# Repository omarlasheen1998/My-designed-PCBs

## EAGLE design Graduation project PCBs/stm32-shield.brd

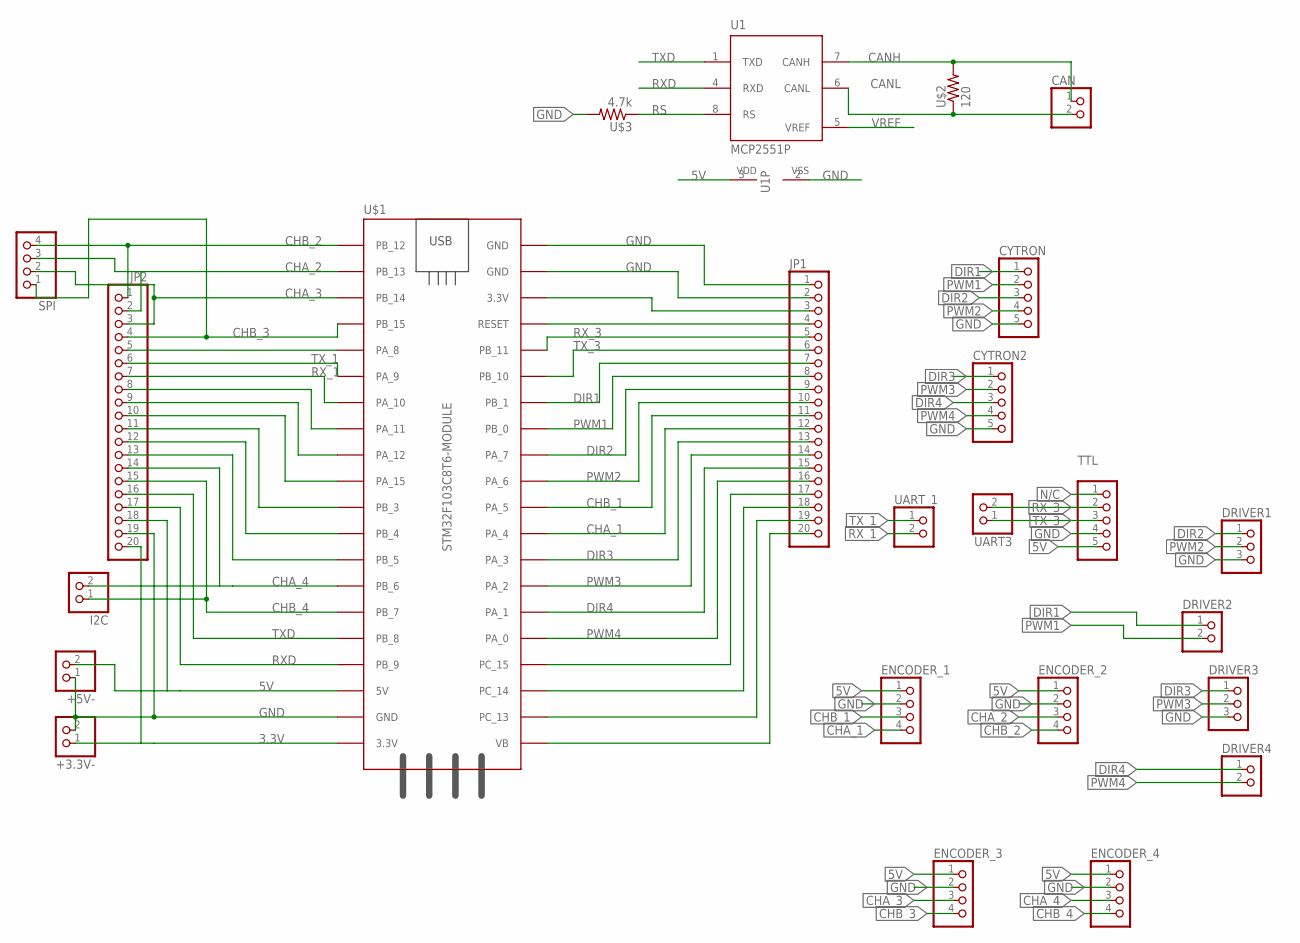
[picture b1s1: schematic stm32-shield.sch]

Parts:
+3.3V-, +5V-: PINHD-2_DATA; 1X02_DATA
CAN: PINHD-2_DATA; 1X02_DATA
CYTRON, CYTRON2: PINHD-5_DATA; 1X05_DATA
DRIVER1, DRIVER3: PINHD-3_DATA; 1X03_DATA
DRIVER2, DRIVER4: PINHD-2_DATA; 1X02_DATA
ENCODER_1, ENCODER_2, ENCODER_3, ENCODER_4: PINHD-4_DATA; 1X04_DATA
I2C: PINHD-2_DATA; 1X02_DATA
JP1, JP2: PINHD-1X20; 1X20
SPI: PINHD-4_DATA; 1X04_DATA
TTL: PINHD-5_DATA; 1X05_DATA
U1: MCP2551P; DIL8
U$1: STM32F103C8T6-MODULE
U$2: 120; 0204/7
U$3: 4.7k; 0204/7
UART3: PINHD-2_DATA; 1X02_DATA
UART_1: PINHD-2_DATA; 1X02_DATA

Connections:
3.3V: +3.3V-.1, JP2.20, U$1.3.3V_1 (3.3V)
5V: +5V-.2, ENCODER_1.1, ENCODER_2.1, ENCODER_3.1, ENCODER_4.1, JP2.18, TTL.5, U1.3 (VDD), U$1.5V
ADADA: JP2.5, U$1.PA_8
ARQRQ: JP2.13, U$1.PB_5
CANH: CAN.1, U1.7 (CANH), U$2.2
CANL: CAN.2, U1.6 (CANL), U$2.1
CHA_1: ENCODER_1.4, JP1.12, U$1.PA_4
CHA_2: ENCODER_2.3, JP2.2, SPI.3, U$1.PB_13
CHA_3: ENCODER_3.3, JP2.3, SPI.2, U$1.PB_14
CHA_4: ENCODER_4.3, I2C.2, JP2.14, U$1.PB_6
CHB_1: ENCODER_1.3, JP1.11, U$1.PA_5
CHB_2: ENCODER_2.4, JP2.1, SPI.4, U$1.PB_12
CHB_3: ENCODER_3.4, JP2.4, SPI.1, U$1.PB_15
CHB_4: ENCODER_4.4, I2C.1, JP2.15, U$1.PB_7
DIR1: CYTRON.1, DRIVER2.1, JP1.7, U$1.PB_1
DIR2: CYTRON.3, DRIVER1.1, JP1.9, U$1.PA_7
DIR3: CYTRON2.1, DRIVER3.1, JP1.13, U$1.PA_3
DIR4: CYTRON2.3, DRIVER4.1, JP1.15, U$1.PA_1
GND: +3.3V-.2, +5V-.1, CYTRON.5, CYTRON2.5, DRIVER1.3, DRIVER3.3, ENCODER_1.2, ENCODER_2.2, ENCODER_3.2, ENCODER_4.2, JP1.1, JP1.2, JP2.19, TTL.4, U1.2 (VSS), U$1.GND_1 (GND), U$1.GND_2 (GND), U$1.GND_3 (GND), U$3.2
unnamed: JP1.3, U$1.3.3V_2 (3.3V)
unnamed: JP1.4, U$1.RESET
unnamed: JP1.17, U$1.PC_15
unnamed: JP1.18, U$1.PC_14
unnamed: JP1.19, U$1.PC_13
unnamed: JP1.20, U$1.VB
unnamed: JP2.8, U$1.PA_11
unnamed: JP2.9, U$1.PA_12
unnamed: JP2.10, U$1.PA_15
unnamed: JP2.11, U$1.PB_3
unnamed: JP2.12, U$1.PB_4
N/C: TTL.1
PWM1: CYTRON.2, DRIVER2.2, JP1.8, U$1.PB_0
PWM2: CYTRON.4, DRIVER1.2, JP1.10, U$1.PA_6
PWM3: CYTRON2.2, DRIVER3.2, JP1.14, U$1.PA_2
PWM4: CYTRON2.4, DRIVER4.2, JP1.16, U$1.PA_0
RS: U1.8 (RS), U$3.1
RXD: JP2.17, U1.4 (RXD), U$1.PB_9
RX_1: JP2.7, U$1.PA_10, UART_1.2
RX_3: JP1.5, TTL.2, U$1.PB_11, UART3.2
TXD: JP2.16, U1.1 (TXD), U$1.PB_8
TX_1: JP2.6, U$1.PA_9, UART_1.1
TX_3: JP1.6, TTL.3, U$1.PB_10, UART3.1
VREF: U1.5 (VREF)

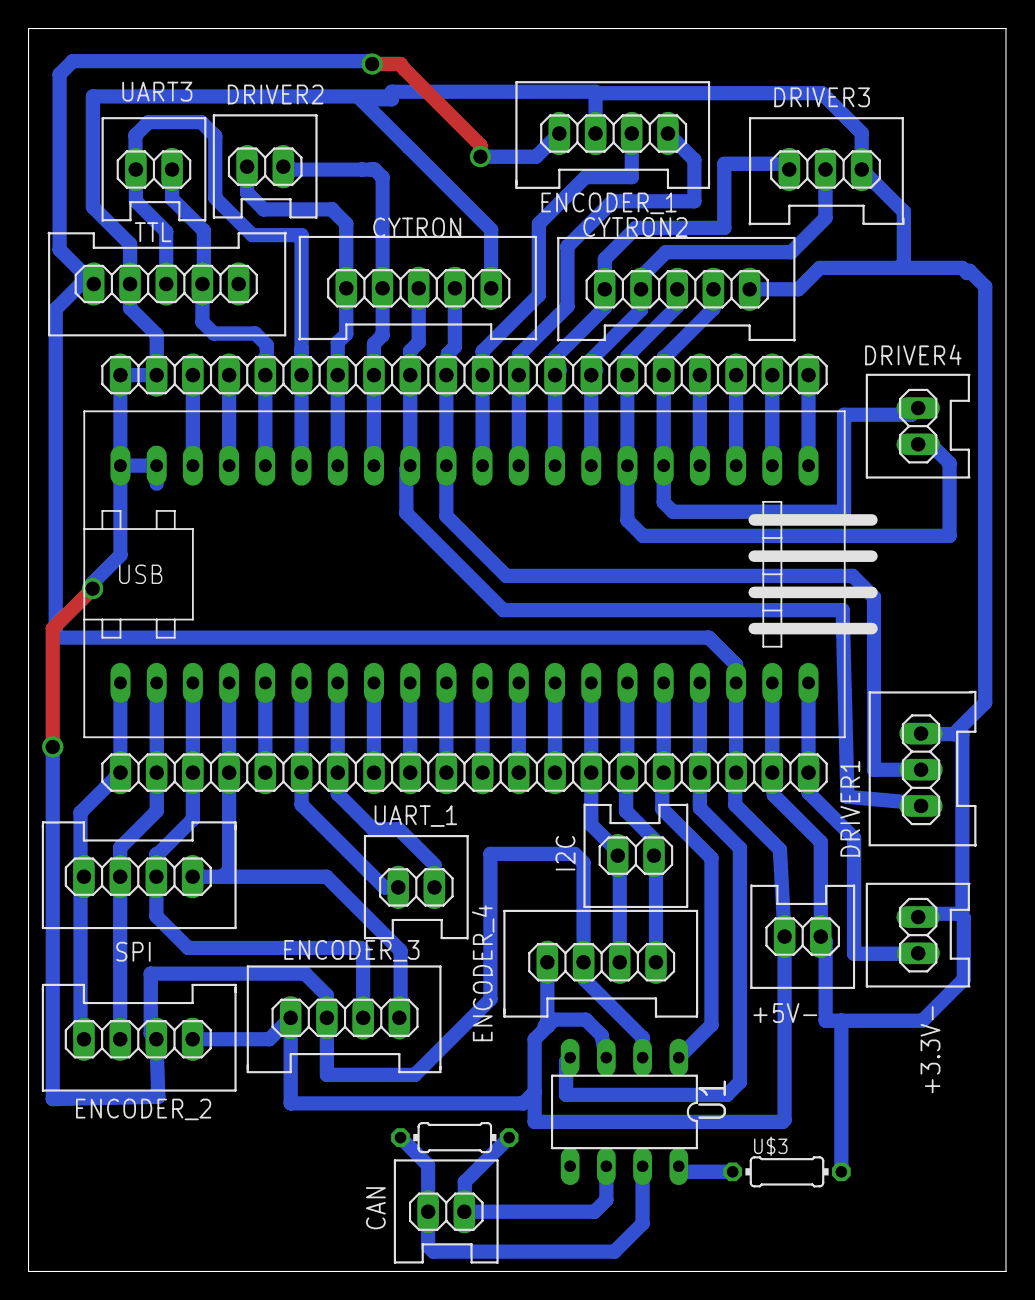
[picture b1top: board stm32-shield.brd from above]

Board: 2 copper layers, 68.6 x 87.2 mm, 24 parts (0 on the bottom side), 41 nets.

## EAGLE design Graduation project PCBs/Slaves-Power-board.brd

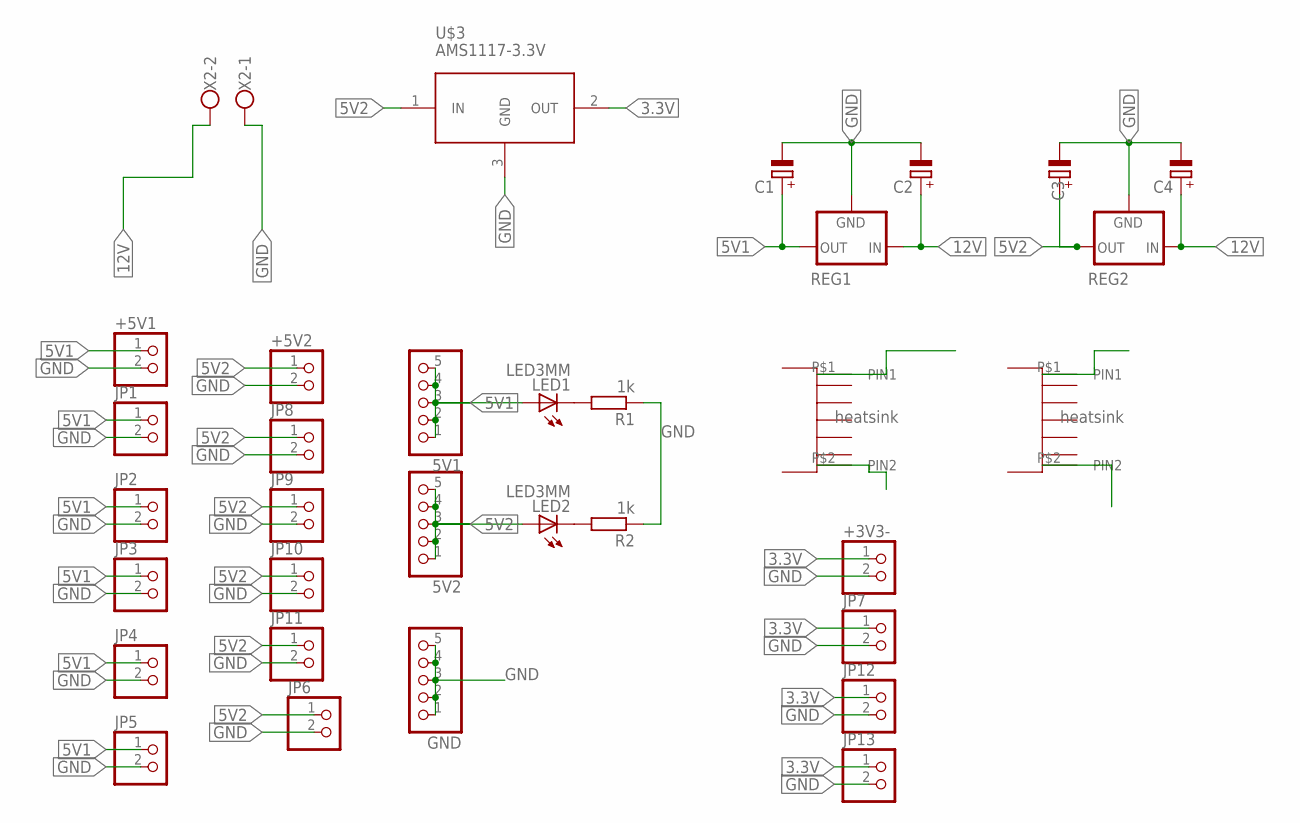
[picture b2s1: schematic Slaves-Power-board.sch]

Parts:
5V1, 5V2: PINHD-1X5; 1X05
+3V3-, +5V1, +5V2: PINHD-2_DATA; 1X02_DATA
C1, C2, C3, C4: CAP_POL; E3,5-8
GND: PINHD-1X5; 1X05
JP1, JP2, JP3, JP4, JP5, JP6, JP7, JP8, JP9, JP10, JP11, JP12, JP13: PINHD-2_DATA; 1X02_DATA
LED1, LED2: LED3MM
R1, R2: 1k; 0204/7
REG1, REG2: 78XXS
U$1, U$2: HEAT-SINK; HEAT_SINK
U$3: AMS1117-3.3V; REG-AMS1117-3P#V
X2: ROSTA.POWER; W239-302

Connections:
3.3V: +3V3-.1, JP7.1, JP12.1, JP13.1, U$3.2 (OUT)
5V1: 5V1.1, 5V1.2, 5V1.3, 5V1.4, 5V1.5, +5V1.1, C1.+, JP1.1, JP2.1, JP3.1, JP4.1, JP5.1, LED1.A, REG1.OUT
5V2: 5V2.1, 5V2.2, 5V2.3, 5V2.4, 5V2.5, +5V2.1, C3.+, JP6.1, JP8.1, JP9.1, JP10.1, JP11.1, LED2.A, REG2.OUT, U$3.1 (IN)
12V: C2.+, C4.+, REG1.IN, REG2.IN, X2.2
GND: +3V3-.2, +5V1.2, +5V2.2, C1.-, C2.-, C3.-, C4.-, GND.1, GND.2, GND.3, GND.4, GND.5, JP1.2, JP2.2, JP3.2, JP4.2, JP5.2, JP6.2, JP7.2, JP8.2, JP9.2, JP10.2, JP11.2, JP12.2, JP13.2, R1.1, R2.1, REG1.GND, REG2.GND, U$3.3 (GND), X2.1
unnamed: LED1.K (C), R1.2
unnamed: LED2.K (C), R2.2

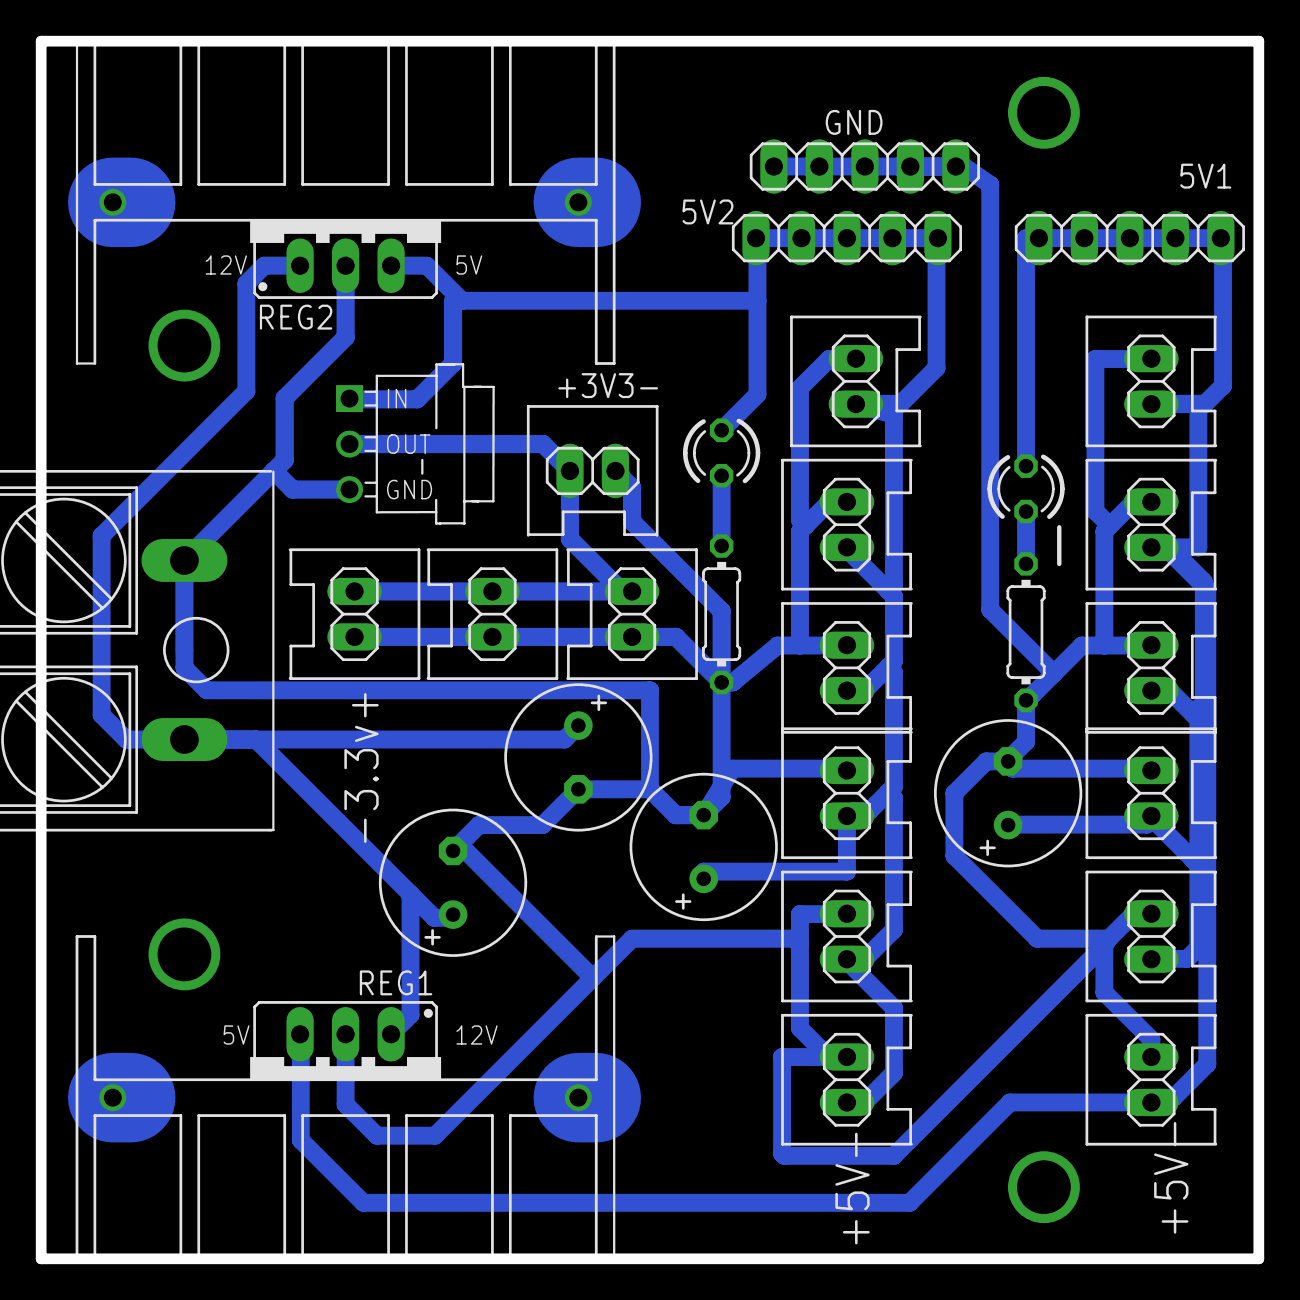
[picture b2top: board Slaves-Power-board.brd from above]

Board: 2 copper layers, 68.0 x 68.0 mm, 33 parts (0 on the bottom side), 7 nets.

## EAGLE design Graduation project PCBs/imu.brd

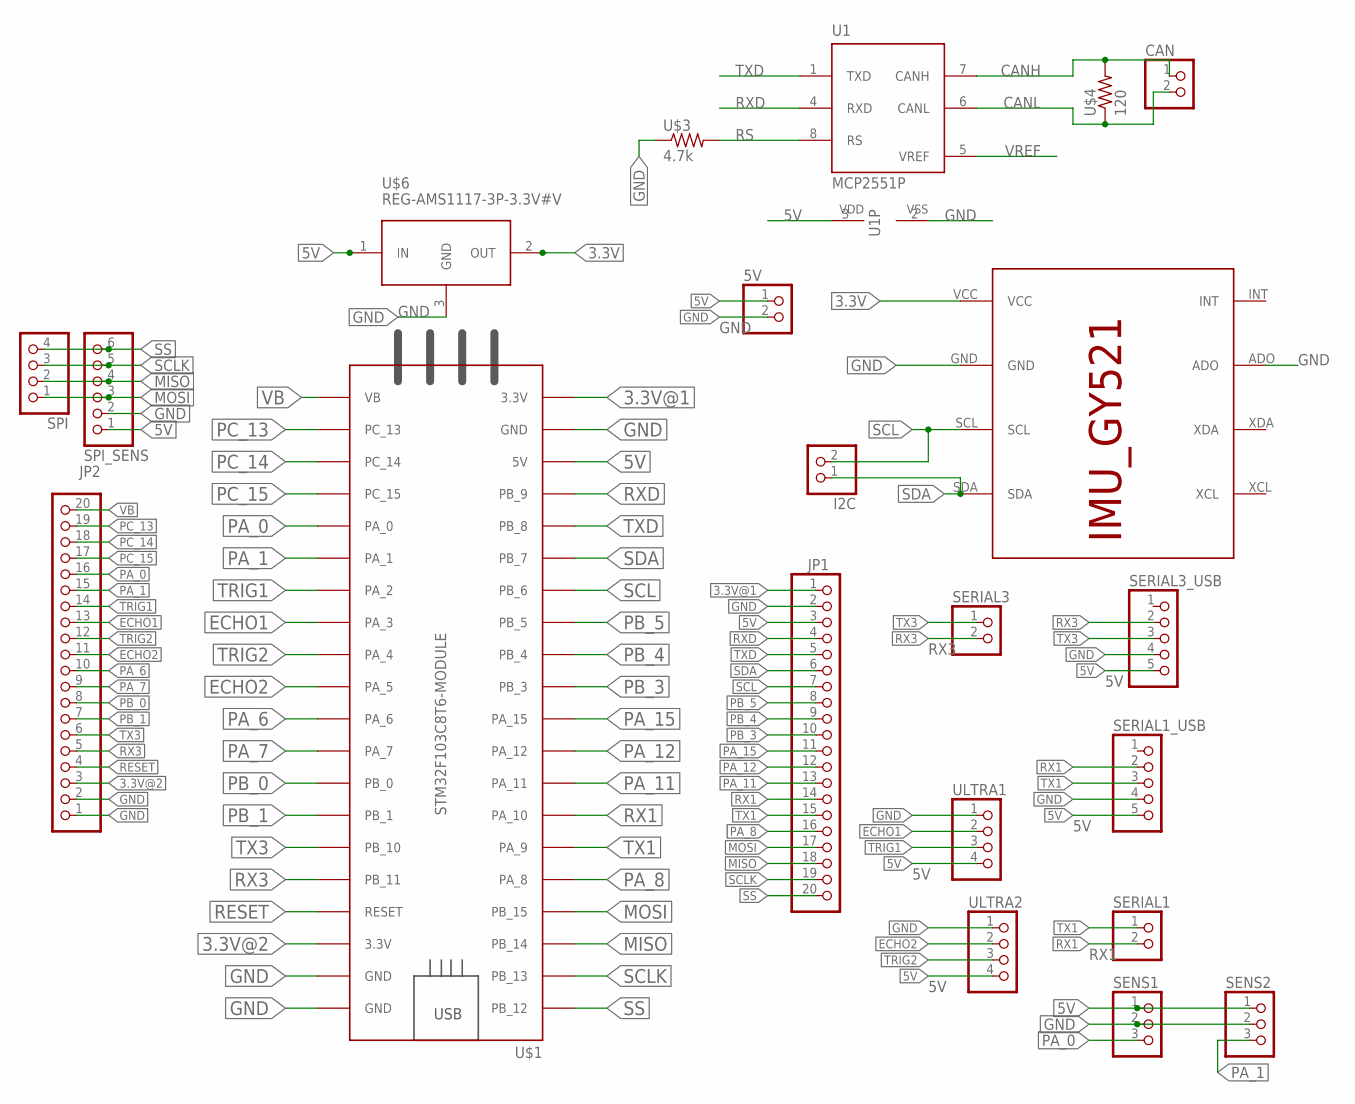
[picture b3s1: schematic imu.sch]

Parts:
5V: PINHD-2_DATA; 1X02_DATA
CAN: PINHD-2_DATA; 1X02_DATA
I2C: PINHD-2_DATA; 1X02_DATA
JP1, JP2: PINHD-1X20; 1X20
SENS1, SENS2: PINHD-3_DATA; 1X03_DATA
SERIAL1, SERIAL3: PINHD-2_DATA; 1X02_DATA
SERIAL1_USB, SERIAL3_USB: PINHD-5_DATA; 1X05_DATA
SPI: PINHD-4_DATA; 1X04_DATA
SPI_SENS: PINHD-6_DATA; 1X06_DATA
U1: MCP2551P; DIL8
U$1: STM32F103C8T6-MODULE
U$2: IMU_MPU6050; IMU_GY521
U$3: 4.7k; 0204/7
U$4: 120; 0204/7
U$6: REG-AMS1117-3P-3.3V#V; REG-AMS1117-3P#V
ULTRA1, ULTRA2: PINHD-4_DATA; 1X04_DATA

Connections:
3.3V: U$2.VCC, U$6.2 (OUT)
3.3V@1: JP1.1, U$1.3.3V_1 (3.3V)
3.3V@2: JP2.3, U$1.3.3V_2 (3.3V)
5V: 5V.1, JP1.3, SENS1.1, SENS2.1, SERIAL1_USB.5, SERIAL3_USB.5, SPI_SENS.1, U1.3 (VDD), U$1.5V, U$6.1 (IN), ULTRA1.4, ULTRA2.4
CANH: CAN.1, U1.7 (CANH), U$4.2
CANL: CAN.2, U1.6 (CANL), U$4.1
ECHO1: JP2.13, U$1.PA_3, ULTRA1.2
ECHO2: JP2.11, U$1.PA_5, ULTRA2.2
GND: 5V.2, JP1.2, JP2.1, JP2.2, SENS1.2, SENS2.2, SERIAL1_USB.4, SERIAL3_USB.4, SPI_SENS.2, U1.2 (VSS), U$1.GND_1 (GND), U$1.GND_2 (GND), U$1.GND_3 (GND), U$2.ADO, U$2.GND, U$3.1, U$6.3 (GND), ULTRA1.1, ULTRA2.1
MISO: JP1.18, SPI.2, SPI_SENS.4, U$1.PB_14
MOSI: JP1.17, SPI.1, SPI_SENS.3, U$1.PB_15
PA_0: JP2.16, SENS1.3, U$1.PA_0
PA_1: JP2.15, SENS2.3, U$1.PA_1
PA_6: JP2.10, U$1.PA_6
PA_7: JP2.9, U$1.PA_7
PA_8: JP1.16, U$1.PA_8
PA_11: JP1.13, U$1.PA_11
PA_12: JP1.12, U$1.PA_12
PA_15: JP1.11, U$1.PA_15
PB_0: JP2.8, U$1.PB_0
PB_1: JP2.7, U$1.PB_1
PB_3: JP1.10, U$1.PB_3
PB_4: JP1.9, U$1.PB_4
PB_5: JP1.8, U$1.PB_5
PC_13: JP2.19, U$1.PC_13
PC_14: JP2.18, U$1.PC_14
PC_15: JP2.17, U$1.PC_15
RESET: JP2.4, U$1.RESET
RS: U1.8 (RS), U$3.2
RX1: JP1.14, SERIAL1.2, SERIAL1_USB.2, U$1.PA_10
RX3: JP2.5, SERIAL3.2, SERIAL3_USB.2, U$1.PB_11
RXD: JP1.4, U1.4 (RXD), U$1.PB_9
SCL: I2C.2, JP1.7, U$1.PB_6, U$2.SCL
SCLK: JP1.19, SPI.3, SPI_SENS.5, U$1.PB_13
SDA: I2C.1, JP1.6, U$1.PB_7, U$2.SDA
SS: JP1.20, SPI.4, SPI_SENS.6, U$1.PB_12
TRIG1: JP2.14, U$1.PA_2, ULTRA1.3
TRIG2: JP2.12, U$1.PA_4, ULTRA2.3
TX1: JP1.15, SERIAL1.1, SERIAL1_USB.3, U$1.PA_9
TX3: JP2.6, SERIAL3.1, SERIAL3_USB.3, U$1.PB_10
TXD: JP1.5, U1.1 (TXD), U$1.PB_8
VB: JP2.20, U$1.VB
VREF: U1.5 (VREF)

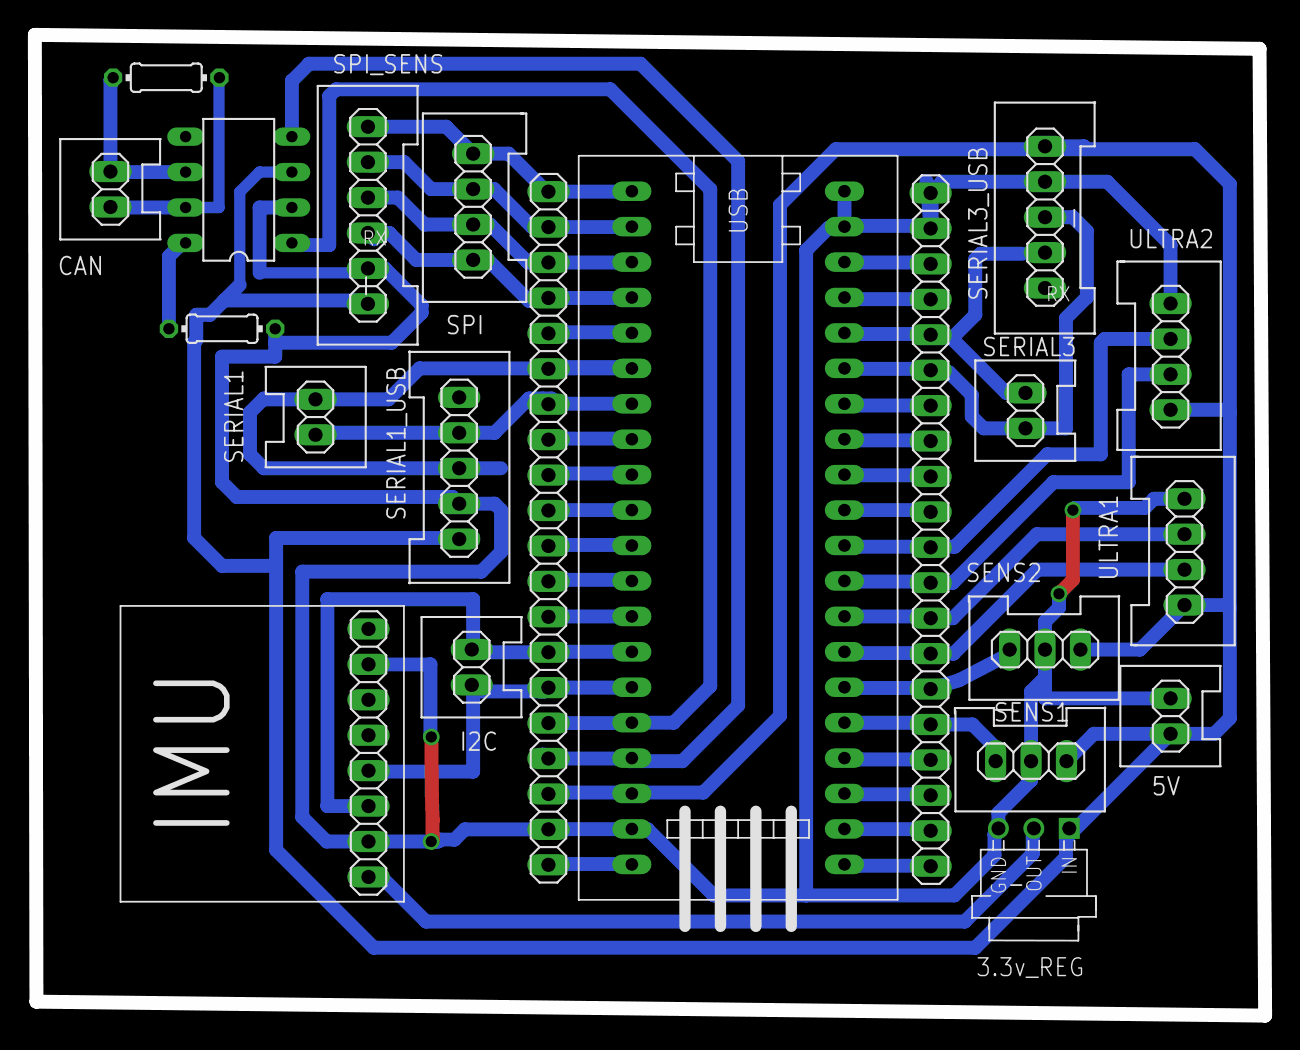
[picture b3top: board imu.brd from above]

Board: 2 copper layers, 88.2 x 70.3 mm, 21 parts (0 on the bottom side), 42 nets.

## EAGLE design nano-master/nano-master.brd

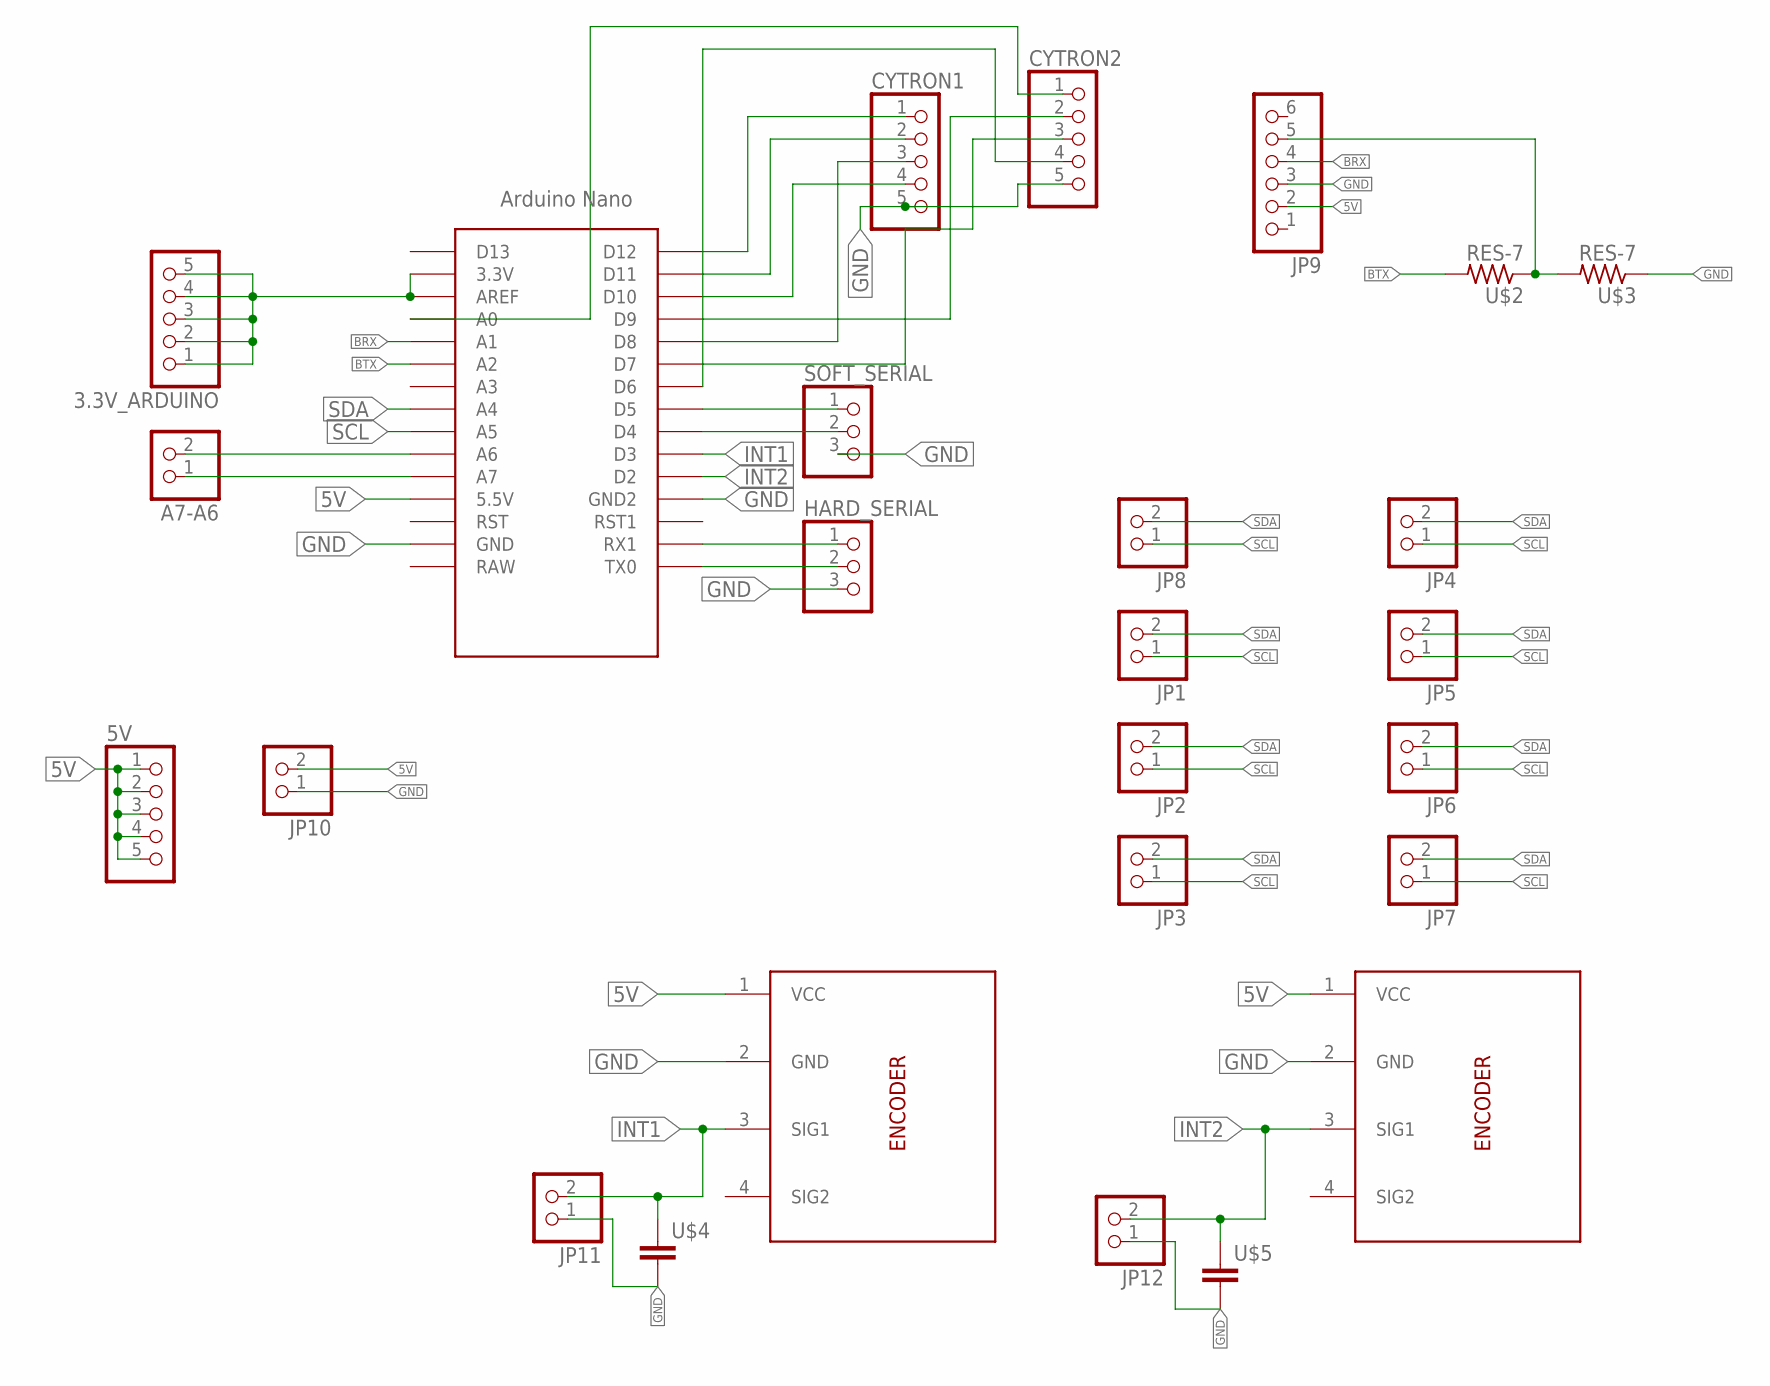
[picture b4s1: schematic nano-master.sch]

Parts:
3.3V_ARDUINO, 5V: PINHD-1X5; 1X05
A7-A6: PINHD-1X2; 1X02
CYTRON1, CYTRON2: PINHD-1X5; 1X05
ENCODER1, ENCODER2: ENCODER; 1X04
HARD_SERIAL: PINHD-1X3; 1X03
JP1, JP2, JP3, JP4, JP5, JP6, JP7, JP8, JP10, JP11, JP12: PINHD-2_DATA; 1X02
JP9: PINHD-1X6; 1X06
SOFT_SERIAL: PINHD-1X3; 1X03
U$1: NANO
U$2, U$3: RES-7; 0204/7
U$4, U$5: CAPACITOR; C025-025X050

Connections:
5V: 5V.1, 5V.2, 5V.3, 5V.4, 5V.5, ENCODER1.1 (VCC), ENCODER2.1 (VCC), JP9.2, JP10.2, U$1.5V (5.5V)
BRX: JP9.4, U$1.A1
BTX: U$1.A2, U$2.2
GND: CYTRON1.5, CYTRON2.5, ENCODER1.2 (GND), ENCODER2.2 (GND), HARD_SERIAL.3, JP9.3, JP10.1, JP11.1, JP12.1, SOFT_SERIAL.3, U$1.GND, U$1.GND1 (GND2), U$3.1, U$4.2, U$5.2
INT1: ENCODER2.3 (SIG1), JP11.2, U$1.D3, U$4.1
INT2: ENCODER1.3 (SIG1), JP12.2, U$1.D2, U$5.1
unnamed: SOFT_SERIAL.1, U$1.D5
unnamed: SOFT_SERIAL.2, U$1.D4
unnamed: HARD_SERIAL.1, U$1.RX1
unnamed: HARD_SERIAL.2, U$1.TX0
unnamed: CYTRON1.1, U$1.D12
unnamed: CYTRON1.2, U$1.D11
unnamed: CYTRON1.4, U$1.D10
unnamed: CYTRON2.2, U$1.D9
unnamed: CYTRON1.3, U$1.D8
unnamed: CYTRON2.3, U$1.D7
unnamed: CYTRON2.4, U$1.D6
unnamed: CYTRON2.1, U$1.A0
unnamed: JP9.5, U$2.1, U$3.2
unnamed: A7-A6.1, U$1.A7
unnamed: A7-A6.2, U$1.A6
unnamed: 3.3V_ARDUINO.1, 3.3V_ARDUINO.2, 3.3V_ARDUINO.3, 3.3V_ARDUINO.4, 3.3V_ARDUINO.5, U$1.3.3V, U$1.AREF
SCL: JP1.1, JP2.1, JP3.1, JP4.1, JP5.1, JP6.1, JP7.1, JP8.1, U$1.A5
SDA: JP1.2, JP2.2, JP3.2, JP4.2, JP5.2, JP6.2, JP7.2, JP8.2, U$1.A4

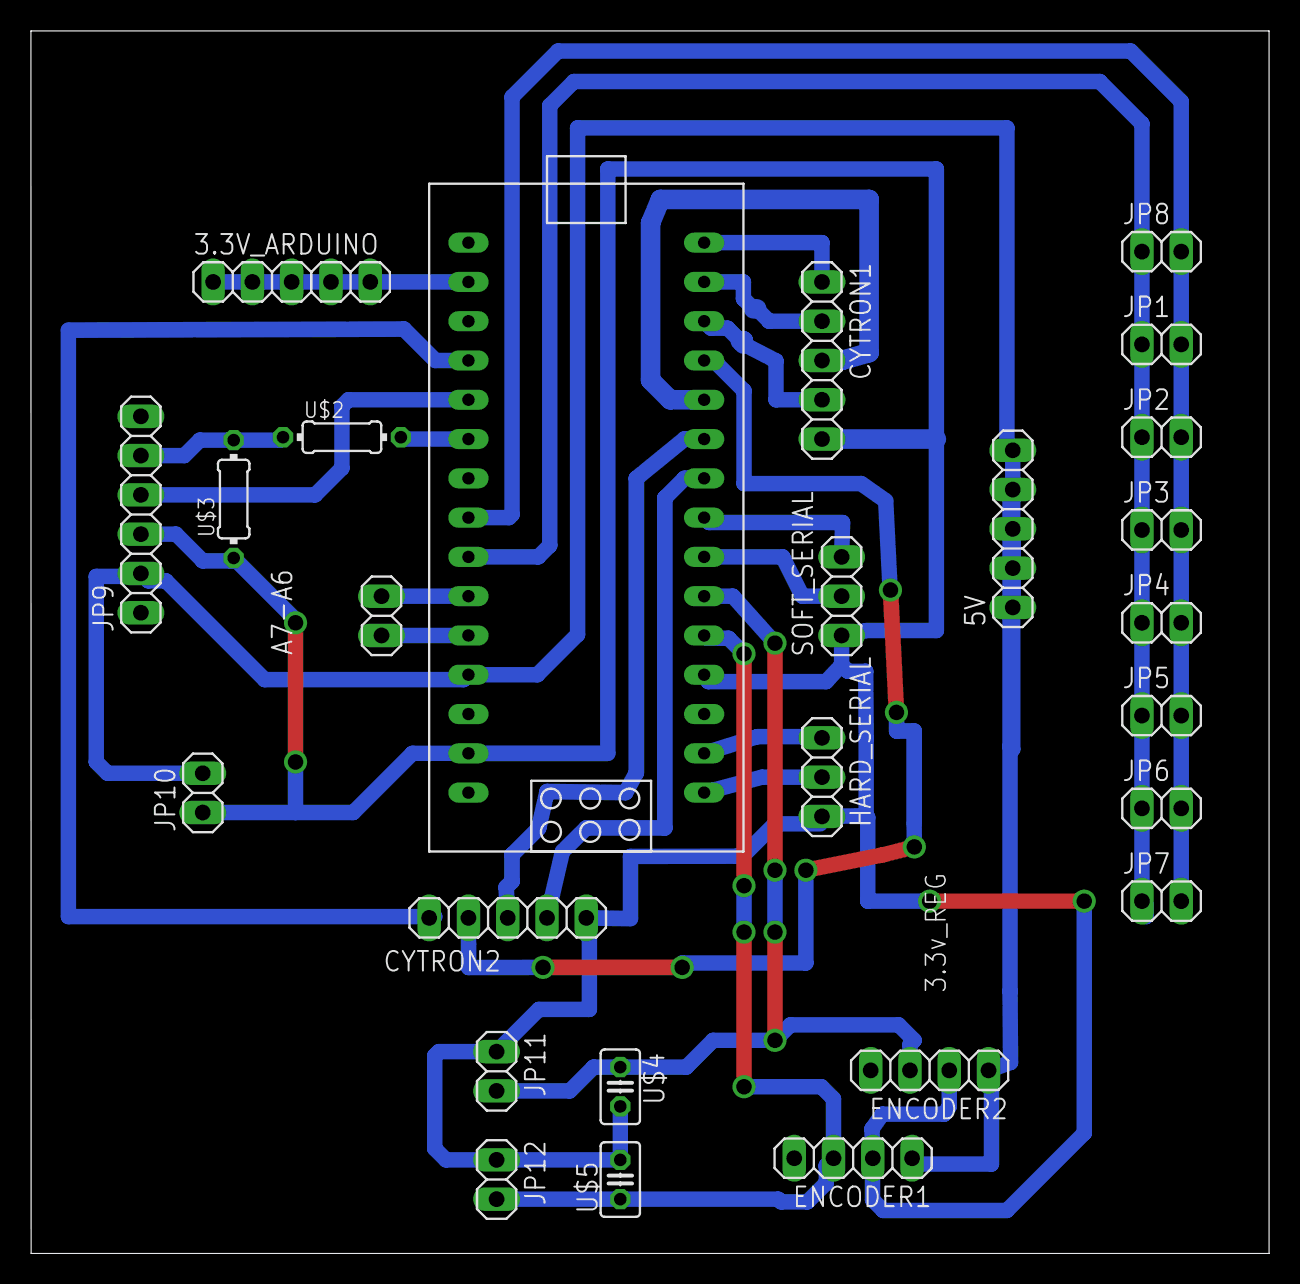
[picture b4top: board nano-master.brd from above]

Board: 2 copper layers, 80.1 x 79.1 mm, 26 parts (0 on the bottom side), 24 nets.

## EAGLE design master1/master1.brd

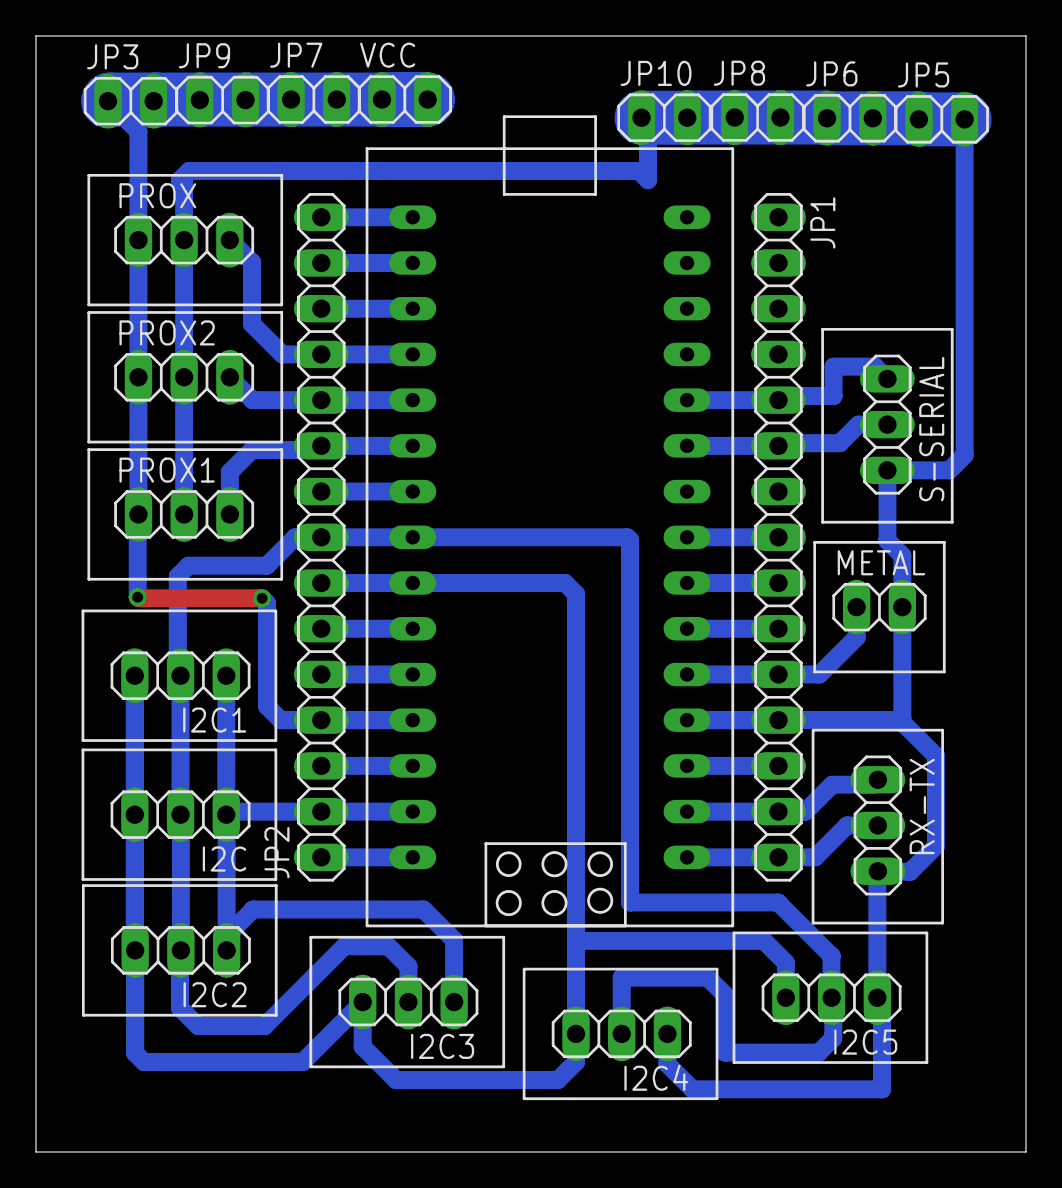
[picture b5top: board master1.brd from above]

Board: 2 copper layers, 55.0 x 62.0 mm, 23 parts (0 on the bottom side), 29 nets.

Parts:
I2C, I2C1, I2C2, I2C3, I2C4, I2C5: 1X03_DATA
JP1, JP2: 1X15
JP3, JP5, JP6, JP7, JP8, JP9, JP10: 1X02
METAL: 1X02_DATA
PROX, PROX1, PROX2: 1X03_DATA
RX-TX: 1X03_DATA
S-SERIAL: 1X03_DATA
U$1: ARDUINO_NANO; NANO
VCC: 1X02

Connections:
A0: JP2.12, PROX.3, U$1.A0
A1: JP2.11, PROX2.3, U$1.A1
A2: JP2.10, PROX1.3, U$1.A2
GND: I2C.1, I2C1.1, I2C2.1, I2C3.1, I2C4.1, I2C5.1, JP1.12, JP2.2, JP5.1, JP5.2, JP6.1, JP6.2, JP8.1, JP8.2, JP10.1, JP10.2, METAL.2, PROX.2, PROX1.2, PROX2.2, RX-TX.3, S-SERIAL.3, U$1.GND, U$1.GND1
unnamed: JP2.1, U$1.RAW
unnamed: JP1.3, U$1.D10
unnamed: JP2.3, U$1.RST
unnamed: JP1.2, U$1.D11
unnamed: JP2.5, U$1.A7
unnamed: JP2.6, U$1.A6
unnamed: JP2.9, U$1.A3
unnamed: JP2.13, U$1.AREF
unnamed: JP2.14, U$1.3.3V
unnamed: JP2.15, U$1.D13
unnamed: JP1.1, U$1.D12
unnamed: JP1.4, U$1.D9
unnamed: JP1.7, U$1.D6
unnamed: JP1.8, U$1.D5
unnamed: JP1.9, U$1.D4
unnamed: JP1.10, U$1.D3
unnamed: JP1.11, METAL.1, U$1.D2
unnamed: JP1.13, U$1.RST1
unnamed: JP1.14, RX-TX.1, U$1.RX1
unnamed: JP1.15, RX-TX.2, U$1.TX0
R-SERIAL: JP1.6, S-SERIAL.2, U$1.D7
SCL: I2C.3, I2C1.3, I2C2.3, I2C3.3, I2C4.3, I2C5.3, JP2.7, U$1.A5
SDA: I2C.2, I2C1.2, I2C2.2, I2C3.2, I2C4.2, I2C5.2, JP2.8, U$1.A4
T-SERIAL: JP1.5, S-SERIAL.1, U$1.D8
VCC: JP2.4, JP3.1, JP3.2, JP7.1, JP7.2, JP9.1, JP9.2, PROX.1, PROX1.1, PROX2.1, U$1.5V, VCC.1, VCC.2

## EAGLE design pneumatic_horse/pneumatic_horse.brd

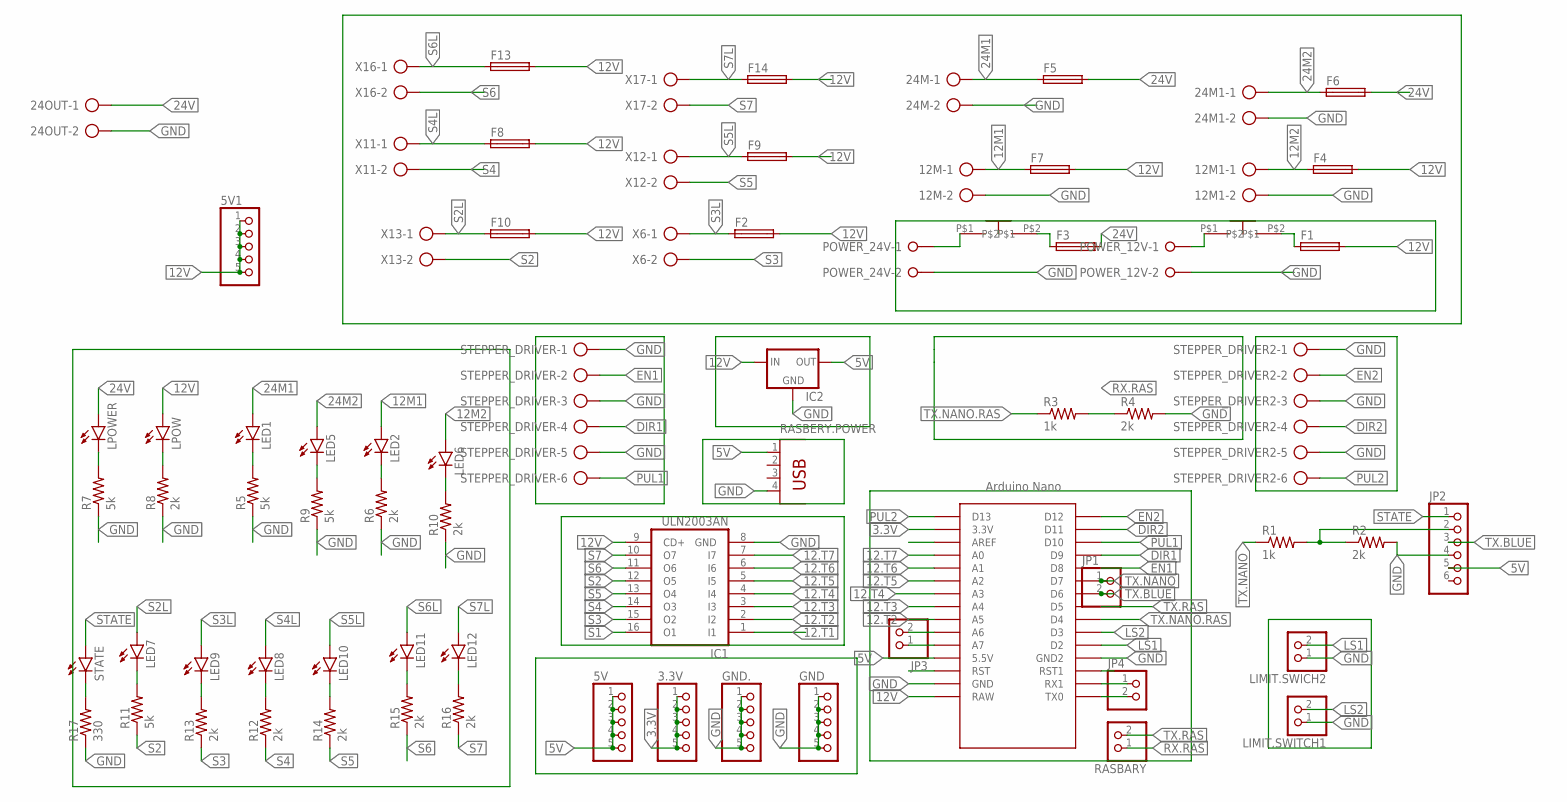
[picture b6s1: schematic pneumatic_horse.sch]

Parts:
3.3V, 5V, 5V1: PINHD-1X5; 1X05
12M, 12M1, 24M, 24M1, 24OUT: AK300/2
F1, F2, F3, F4, F5, F6, F7, F8, F9, F10, F13, F14: SH22,5A
GND, GND.: PINHD-1X5; 1X05
IC1: ULN2003AN; DIL16
IC2: 78XXS
JP1, JP3, JP4: PINHD-1X2; 1X02
JP2: PINHD-1X6; 1X06
LED1, LED2, LED5, LED6, LED7, LED8, LED9, LED10, LED11, LED12: LED3MM
LIMIT.SWICH2, LIMIT.SWITCH1: PINHD-1X2; 1X02
LPOW: LED5MM
LPOWER: LED3MM
POWER_12V, POWER_24V: W237-2N
R1, R3: 1k; 0204/7
R2, R4, R6, R8, R10: 2k; 0204/7
R5, R7, R9: 5k; 0204/7
R11: 5k; 0204/5
R12, R13, R14, R15, R16: 2k; 0204/5
R17: 330; 0204/5
RASBARY: PINHD-1X2; 1X02
RASBERY.POWER: PN87520
STATE: LED3MM
STEPPER_DRIVER, STEPPER_DRIVER2: AK300/6
U$1: NANO
U$2, U$3: ON_OFF
X6, X11, X12, X13, X16, X17: AK300/2

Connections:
3.3V: 3.3V.1, 3.3V.2, 3.3V.3, 3.3V.4, 3.3V.5, U$1.3.3V
5V: 5V.1, 5V.2, 5V.3, 5V.4, 5V.5, IC2.OUT, JP2.5, RASBERY.POWER.1, U$1.5V (5.5V)
12.T1: IC1.1 (I1)
12.T2: IC1.2 (I2), U$1.A5
12.T3: IC1.3 (I3), U$1.A4
12.T4: IC1.4 (I4), U$1.A3
12.T5: IC1.5 (I5), U$1.A2
12.T6: IC1.6 (I6), U$1.A1
12.T7: IC1.7 (I7), U$1.A0
12M1: 12M.1, F7.1, LED2.A
12M2: 12M1.1, F4.1, LED6.A
12V: 5V1.1, 5V1.2, 5V1.3, 5V1.4, 5V1.5, F1.2, F2.2, F4.2, F7.2, F8.2, F9.2, F10.2, F13.2, F14.2, IC1.9 (CD+), IC2.IN, LPOW.A, U$1.RAW
24M1: 24M.1, F5.1, LED1.A
24M2: 24M1.1, F6.1, LED5.A
24V: 24OUT.1, F3.2, F5.2, F6.2, LPOWER.A
DIR1: STEPPER_DRIVER.4, U$1.D9
DIR2: STEPPER_DRIVER2.4, U$1.D11
EN1: STEPPER_DRIVER.2, U$1.D8
EN2: STEPPER_DRIVER2.2, U$1.D12
GND: 12M.2, 12M1.2, 24M.2, 24M1.2, 24OUT.2, GND.1, GND.2, GND.3, GND.4, GND.5, GND..1, GND..2, GND..3, GND..4, GND..5, IC1.8 (GND), IC2.GND, JP2.4, LIMIT.SWICH2.1, LIMIT.SWITCH1.1, POWER_12V.2, POWER_24V.2, R2.2, R4.2, R5.1, R6.1, R7.1, R8.1, R9.1, R10.1, R17.1, RASBERY.POWER.4, STEPPER_DRIVER.1, STEPPER_DRIVER.3, STEPPER_DRIVER.5, STEPPER_DRIVER2.1, STEPPER_DRIVER2.3, STEPPER_DRIVER2.5, U$1.GND, U$1.GND1 (GND2)
LS1: LIMIT.SWICH2.2, U$1.D2
LS2: LIMIT.SWITCH1.2, U$1.D3
unnamed: POWER_24V.1, U$2.P$1
unnamed: LED1.K (C), R5.2
unnamed: F3.1, U$2.P$2
unnamed: LED2.K (C), R6.2
unnamed: LED5.K (C), R9.2
unnamed: LED6.K (C), R10.2
unnamed: LED7.K (C), R11.2
unnamed: LPOWER.K (C), R7.2
unnamed: LPOW.K (C), R8.2
unnamed: LED8.K (C), R12.2
unnamed: JP4.1, U$1.RX1
unnamed: JP4.2, U$1.TX0
unnamed: LED9.K (C), R13.2
unnamed: LED10.K (C), R14.2
unnamed: LED11.K (C), R15.2
unnamed: LED12.K (C), R16.2
unnamed: JP3.1, U$1.A7
unnamed: JP3.2, U$1.A6
unnamed: JP2.2, R1.2, R2.1
unnamed: R17.2, STATE.K (C)
unnamed: POWER_12V.1, U$3.P$1
unnamed: F1.1, U$3.P$2
PUL1: STEPPER_DRIVER.6, U$1.D10
PUL2: STEPPER_DRIVER2.6, U$1.D13
RX.RAS: R3.2, R4.1, RASBARY.1
S1: IC1.16 (O1)
S2: IC1.12 (O5), R11.1, X13.2
S2L: F10.1, LED7.A, X13.1
S3: IC1.15 (O2), R13.1, X6.2
S3L: F2.1, LED9.A, X6.1
S4: IC1.14 (O3), R12.1, X11.2
S4L: F8.1, LED8.A, X11.1
S5: IC1.13 (O4), R14.1, X12.2
S5L: F9.1, LED10.A, X12.1
S6: IC1.11 (O6), R15.1, X16.2
S6L: F13.1, LED11.A, X16.1
S7: IC1.10 (O7), R16.1, X17.2
S7L: F14.1, LED12.A, X17.1
STATE: JP2.1, STATE.A
TX.BLUE: JP1.2, JP2.3, U$1.D6
TX.NANO: JP1.1, R1.1, U$1.D7
TX.NANO.RAS: R3.1, U$1.D4
TX.RAS: RASBARY.2, U$1.D5

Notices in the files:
parts and their libraries:
diy-modules: Released under the Creative Commons Attribution 4.0 International License: http://creativecommons.org/licenses/by/4.0
